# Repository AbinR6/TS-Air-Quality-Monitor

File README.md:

# TS Air Quality Monitor

An embedded environmental monitoring system engineered for continuous, real-time indoor air quality observation, particulate matter tracking, CO₂ sensing, and wireless telemetry.

---

## 📷 Hardware & Prototype Gallery

---

## 📁 Repository Structure

```
.
├── AirMonitor/                 # Complete embedded firmware, software & documentation
│   ├── 01_Evidence/            # Test and validation evidence
│   ├── 02_Hardware/            # Schematic, PCB layouts, KiCad files, BOM
│   ├── 03_Traceability/        # Requirements and traceability matrix
│   ├── 04_Firmware/            # STM32 HAL / C modular firmware
│   ├── 05_Software/            # Python provisioning, telemetry & inspection tools
│   ├── 06_Tools/               # Analysis scripts and test utilities
│   ├── 07_Documentation/       # Architecture, Calibration, Hardware, Firmware docs
│   ├── 08_Models/              # 3D enclosure and CAD models (.stl)
│   ├── 09_Validation/          # Environmental and system validation test plans
│   ├── config/                 # Example device and MQTT configuration
│   └── README.md               # Detailed system architecture and firmware documentation
├── pictures/                   # High-resolution hardware and assembly photos
└── .vscode/                    # VS Code workspace settings
```

For the comprehensive engineering methodology, system block diagrams, register maps, and flashing guides, refer to the [AirMonitor README](AirMonitor/README.md).

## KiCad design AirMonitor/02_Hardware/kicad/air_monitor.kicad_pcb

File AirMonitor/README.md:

# Air Monitor

An embedded environmental monitoring system built around the STM32F407ZGT6 microcontroller, integrating particulate, CO₂, temperature/humidity sensing, display interaction, power management, and telemetry.

---

## 1. Project Overview

The **Air Monitor** is an integrated indoor environmental sensing station engineered for continuous, real-time air quality observation. The device combines laser-scattering particulate measurement, optical non-dispersive infrared (NDIR) carbon dioxide sensing, and precision climate telemetry in a compact, standalone form factor.

An ARM Cortex-M4 32-bit RISC microcontroller (STM32F407ZGT6) runs a modular firmware pipeline that processes raw sensor signals, calculates the standard United States Environmental Protection Agency (US EPA) Air Quality Index (AQI), renders visual dashboards on a color IPS display, manages single-cell lithium-ion battery charging, and outputs structured telemetry.

```
+----------------------------------------------------------------------------------------------------+
|                                    AIR MONITOR SYSTEM ARCHITECTURE                                 |
+----------------------------------------------------------------------------------------------------+

   POWER DOMAIN                                              COMPUTE DOMAIN
   =============                                             ==============
  +------------------+
  | USB Type-C (5V)  |-----+
  +------------------+     |
                           v
  +------------------+  +--------------------+               +--------------------------------------+
  | 18650 Li-Ion     |->| Charger & PowerPath|               |        STM32F407ZGT6 MCU             |
  | 3.7V / 2500 mAh  |  | (BQ24040 / MCP73831)               |  - ARM Cortex-M4 @ 168 MHz with FPU  |
  +------------------+  +--------------------+               |  - 1024 KB (1 MB) Flash              |
                           |                                 |  - 192 KB SRAM (128KB + 64KB CCM)    |
                           | (VBAT / VBUS)                   |  - Package: LQFP-144 (20x20 mm)      |
                           v                                 +--------------------------------------+
                        +--------------------+                                  |
                        | 3.3V Buck Regulator|----------------------------------+ (3.3V VDD_MCU)
                        | (TPS62088 / SY8089)|
                        +--------------------+
                                   | (3.3V System Rail)
                                   +-------------------------+--------------------+
                                   |                         |                    |
                                   v                         v                    v
   SENSOR DOMAIN              +------------+            +------------+       +------------+
   =============              | PM Sensor  |            | CO2 Sensor |       | T/RH Sensor|
                              | Laser PM2.5|            | NDIR / PAS |       | Sensirion  |
                              | (PMS5003)  |            | (SCD41)    |       | (SHT41)    |
                              +------------+            +------------+       +------------+
                                   ^                         ^                    ^
                                   | UART                    | I2C                | I2C
                                   | (Candidate USART)       | (Candidate I2C1)   | (Shared Bus)
                                   |                         |                    |
                                   +-------------------------+--------------------+
                                                             |
   USER INTERFACE DOMAIN                                     |
   =====================                                     v
  +----------------------------+                     +--------------------------------------+
  | 31-Pin SPI TFT Display     |<--------------------| SPI Bus (MOSI, SCLK, CS, DC, RESET)  |
  | 2.1" IPS LCD (ST7789)      |                     | PWM Backlight Driver (TIM PWM)       |
  +----------------------------+                     +--------------------------------------+
  | Capacitive Touch Flex      |<--------------------| I2C Bus / GPIO Interrupt (TOUCH_INT) |
  | `DANY_TOUCH` (Top Slider)  |                     |                                      |
  +----------------------------+                     +--------------------------------------+
```

---

## 2. Key Features

- **Multi-Pollutant Environmental Sensing**:
  - **Particulate Matter (PM1.0, PM2.5, PM10)**: Real-time mass concentration via laser optical scattering (Plantower PMS5003-compatible over UART).
  - **Carbon Dioxide (CO₂)**: Ambient optical sensing (400–5000 ppm) via Sensirion SCD41 photoacoustic NDIR transducer over I²C.
  - **Climate Telemetry**: Precision ambient temperature (-10°C to +60°C, ±0.2°C) and relative humidity (0–100% RH, ±1.8%) via Sensirion SHT41.
- **Onboard Compute & Storage**:
  - STMicroelectronics **STM32F407ZGT6** running at 168 MHz with 1 MB embedded Flash and 192 KB SRAM.
  - Non-volatile storage for device calibration, configuration, and operating profiles.
  - Flash circular ring buffer storing up to 256 offline telemetry records during interface disconnects.
- **Display & User Interaction**:
  - High-resolution 2.1-inch color IPS TFT LCD (240 × 320) driven by Sitronix ST7789V over high-speed 40 MHz SPI.
  - Smooth 5 kHz PWM backlight dimming via low-side N-channel MOSFET driven by timer output.
  - Top capacitive touch slider bar (`DANY_TOUCH` / CST816S) enabling tap, swipe, and long-press navigation.
- **Power Management & Mobility**:
  - Dual power architecture: 5V USB Type-C external input and integrated single-cell 18650 Li-ion rechargeable battery (2500 mAh).
  - Synchronous step-down buck converter (TPS62088) providing high-efficiency 3.3V rail regulation.
  - Linear CC/CV charging controller with charge status telemetry and thermal regulation.
- **Connectivity & Telemetry**:
  - Telemetry streaming via structured JSON payloads.
  - Local discovery and telemetry interface support.
  - Robust offline data buffering in non-volatile memory.

---

## 3. Hardware Subsystem

The custom 4-layer printed circuit board (64.0 mm × 64.0 mm) is engineered for optimal signal integrity, thermal isolation, and mechanical integration:

| Component RefDes | Subsystem | Part Description | Manufacturer | Package / Footprint | Interface |
|:---|:---|:---|:---|:---|:---|
| **U1** | Processing | STM32F407ZGT6 (1MB Flash, 192KB SRAM) | STMicroelectronics | LQFP-144 (20x20 mm) | SPI, UART, I2C, GPIO |
| **U2** | Power | TPS62088 Synchronous Buck (3.3V, 1.5A) | Texas Instruments | SOT-23-6 / SOT-563 | Power Rail |
| **U3** | Power | MCP73831 1S Li-Ion Linear Charger | Microchip Technology | SOT-23-5 / DFN-8 | Power Rail / Status |
| **BAT1** | Power | 18650 Li-Ion Cell (3.7V, 2500mAh) | Industry Standard | 18.2 mm × 65.0 mm | 3-Wire Harness (VBAT/NTC/GND) |
| **M1** | Sensing | Optical Laser Dust Sensor (PM1/2.5/10) | Plantower (PMS5003) | 50.0 mm × 38.0 mm × 21.0 mm | Candidate UART |
| **M2** | Sensing | Photoacoustic NDIR CO₂ Sensor | Sensirion (SCD41) | LGA-8 10.1 mm × 10.1 mm | Candidate I²C |
| **M3** | Sensing | Precision Temperature & Humidity | Sensirion (SHT41) | DFN-4 1.5 mm × 1.5 mm | Candidate I²C |
| **DISP1** | UI | 2.1" Color IPS TFT Display (240×320) | Sitronix (ST7789V) | 31-Pin 0.5mm FPC Tail | Candidate SPI |
| **TOUCH1**| UI | Top Capacitive Touch Flex (`DANY_TOUCH`) | Custom / Hynitron | 6-Pin 0.5mm FPC Ribbon | Candidate I²C / GPIO |
| **J1** | Connector | 31-Pin 0.5mm ZIF FPC Receptacle | Hirose (FH12-31S) | SMT Right-Angle | Display Interface |
| **J2** | Connector | 6-Pin 0.5mm ZIF FPC Receptacle | Hirose (FH12-6S) | SMT Right-Angle | Touch Interface |
| **J3** | Connector | 3-Pin 2.0mm Wafer Header | JST (B3B-PH-K-S) | Through-Hole | Battery Wire Harness |
| **J4** | Connector | USB Type-C 16-Pin Receptacle | Industry Standard | Hybrid SMT / TH | 5V DC Power & Serial |

Hardware engineering files and schematics are located in [`02_Hardware/`](file:///c:/Users/abina/Downloads/STM32%20Project/AirMonitor/02_Hardware/).

---

## 4. Firmware Architecture

The firmware is developed in Embedded C targeting the STM32F407ZGT6 microcontroller utilizing the **STM32 HAL** and STM32Cube framework. It is architected into modular components:

```
04_Firmware/
├── CMakeLists.txt                # CMake build configuration for ARM GCC
├── main/
│   ├── main.c                   # System entrypoint & task dispatch
│   ├── system_init.c            # Power-on self-test & clock bringup (168 MHz)
│   ├── system_init.h            # System initialization headers
│   └── app_config.h             # Global hardware pin allocations & thresholds
├── components/
│   ├── drivers/                 # Hardware abstraction peripheral drivers
│   │   ├── pm_sensor_pms.c      # Plantower PMS UART packet decoder & checksum
│   │   ├── co2_sensor_scd4x.c   # Sensirion SCD41 I2C driver with CRC validation
│   │   ├── trh_sensor_sht4x.c   # Sensirion SHT41 precision T/RH driver
│   │   ├── display_st7789.c     # ST7789 40MHz SPI display driver
│   │   ├── touch_cst816.c       # Capacitive touch gesture state machine
│   │   └── power_driver.c       # Battery ADC and charging status GPIO monitor
│   ├── application/             # Measurement pipeline, AQI & alerts
│   │   ├── measurement_pipeline.c # Outlier filtering & rolling average
│   │   ├── air_quality_index.c  # US EPA AQI calculation engine
│   │   └── alert_manager.c      # Multi-threshold hysteresis alarm manager
│   ├── display/                 # Graphical user interface
│   │   ├── ui_manager.c         # Screen carousel & gesture dispatcher
│   │   ├── ui_screens.c         # Dashboard, detail, and diagnostic screen views
│   │   └── ui_theme.c           # High-contrast color tokens & typography
│   ├── network/                 # Telemetry & communications
│   │   ├── wifi_manager.c       # Network state machine & auto-reconnect
│   │   ├── mqtt_manager.c       # Structured JSON telemetry publisher
│   │   ├── http_server.c        # Local REST API endpoints
│   │   └── telemetry_encoder.c  # JSON telemetry serialization
│   ├── storage/                 # Persistence & caching
│   │   ├── nvs_manager.c        # Flash non-volatile key-value store
│   │   └── telemetry_buffer.c   # Circular ring buffer for offline records
│   ├── calibration/             # Zero-point & span calibration routines
│   ├── configuration/           # Device provisioning & factory profiles
│   ├── diagnostics/             # Peripheral self-test & fault logging
│   └── power/                   # Battery state-of-charge calculation
└── tests/                       # Unit test suites (AQI, parser, ring buffer)
```

### Measurement Pipeline Engine
1. **Sensor Acquisition**: Sensors sampled periodically via dedicated task routines.
2. **Signal Validation**: CRC and checksum verification discard malformed packets.
3. **Filtering**: Exponential Moving Average (EMA) algorithm suppresses environmental noise and transient spikes.
4. **AQI Calculation**: Evaluates US EPA piecewise linear breakpoints for PM2.5, PM10, and CO₂.
5. **UI Rendering**: Renders real-time metrics on the active display screen at ~30 FPS.
6. **Telemetry & Storage**: Serializes data to JSON, transmits via communication interfaces, or buffers to flash if offline.

---

## 5. Software Tools & Simulation Layer

The `05_Software/` directory contains an engineering toolchain for host-side validation, headless CI/CD testing, and telemetry pipeline verification without requiring bench hardware:

- **Virtual Device Simulator** (`05_Software/device_simulator/virtual_device.py`):
  - Simulates the complete environmental monitor state machine.
  - Supports 5 deterministic test scenarios: `NORMAL`, `HIGH_PM`, `HIGH_CO2`, `SENSOR_FAULT`, and `NETWORK_DROP`.
- **Telemetry Receiver Daemon** (`05_Software/telemetry_tools/telemetry_receiver.py`):
  - Ingests JSON telemetry streams and records them to a local SQLite database (`telemetry_store.sqlite3`).
- **Telemetry Inspector CLI** (`05_Software/telemetry_tools/inspect_telemetry.py`):
  - Displays real-time formatted ASCII terminal tables of sensor readings and diagnostic metrics.
- **Packet Schema Analyzer** (`05_Software/inspection_tools/packet_analyzer.py`):
  - Validates telemetry packets against schema constraints and physical sensor limits.
- **Device Provisioning Utility** (`05_Software/configuration_tools/provision_device.py`):
  - Generates configuration JSON payloads for rapid device provisioning.

---

## 6. Repository Structure

```
.
├── 01_Evidence/                 # Hardware optical analysis, inspection records & manifest
├── 02_Hardware/                 # Schematics, PCB layout, BOM, power tree & pin maps
│   ├── kicad/                  # KiCad 8.0 project, schematic, and PCB layout
│   ├── 3d/                     # Mechanical 3D STL assets for PCB and components
│   └── symbols/                # Schematic symbol libraries
├── 03_Traceability/             # Requirements, hardware, firmware & test traceability matrices
├── 04_Firmware/                 # STM32 HAL / C firmware source code & drivers
├── 05_Software/                 # Host-side simulation, telemetry receiver & analysis tools
├── 06_Tools/                    # Repository audit scripts and evidence tooling
├── 07_Documentation/            # Engineering specifications, architectural guides & manuals
├── 08_Models/                   # Mechanical enclosure CAD specification and 3D STL models
├── 09_Validation/               # System validation plans and test procedures
├── config/                      # Example configuration profiles
├── FINAL_PROJECT_COMPLETION_REPORT.md # Engineering sign-off completion report
├── TOOLCHAIN.md                 # Pinned compiler and toolchain specifications
├── CHANGELOG.md                 # Project version release history
└── LICENSE                      # Project software & documentation license
```

---

## 7. Build & Setup Instructions

### 7.1 Firmware Compilation (STM32 HAL / ARM GCC)

Prerequisites: **GNU Arm Embedded Toolchain (`arm-none-eabi-gcc`)** and **CMake** (or STM32CubeIDE).

```bash
# 1. Navigate to the firmware workspace
cd 04_Firmware

# 2. Create build directory
mkdir build && cd build

# 3. Configure CMake with ARM toolchain
cmake -DCMAKE_TOOLCHAIN_FILE=../cmake/arm-none-eabi.cmake ..

# 4. Compile firmware binary
cmake --build .

# 5. Flash target via ST-Link / OpenOCD (SWD)
openocd -f interface/stlink.cfg -f target/stm32f4x.cfg -c "program air_monitor.elf verify reset exit"
```

### 7.2 Running Host Simulation & Telemetry Pipeline

Prerequisites: **Python ≥ 3.10**.

```bash
# 1. Install toolchain dependencies
pip install -r 06_Tools/python/requirements.txt

# 2. Run virtual device simulator in normal operating mode
python 05_Software/device_simulator/virtual_device.py --scenario NORMAL --count 10 --output telemetry_stream.jsonl

# 3. Ingest simulated telemetry stream into SQLite database
python 05_Software/telemetry_tools/telemetry_receiver.py --file telemetry_stream.jsonl

# 4. Inspect recorded metrics
python 05_Software/telemetry_tools/inspect_telemetry.py --limit 10

# 5. Run static repository audit
python 06_Tools/python/validation/repo_audit.py
```

---

## 8. Configuration & Calibration

The system supports runtime configuration via non-volatile storage:

- **Reporting Interval**: Default telemetry frequency is 60 seconds.
- **Sensor Calibration**:
  - Particulate matter linear scaling: $PM_{cal} = (PM_{raw} \times S_{pm}) + O_{pm}$
  - Carbon dioxide zero-point calibration: Baseline 400 ppm fresh air reset via 5-second long press on the top touch slider.
  - Thermal conduction offset: Ambient temperature compensated for internal board heating ($\Delta T = -0.50^\circ\text{C}$).

Full mathematical formulations are documented in [`07_Documentation/CALIBRATION.md`](file:///c:/Users/abina/Downloads/STM32%20Project/AirMonitor/07_Documentation/CALIBRATION.md).

---

## 9. Engineering Documentation Index

Comprehensive technical documentation is maintained in [`07_Documentation/`](file:///c:/Users/abina/Downloads/STM32%20Project/AirMonitor/07_Documentation/):

- [System Architecture](file:///c:/Users/abina/Downloads/STM32%20Project/AirMonitor/07_Documentation/ARCHITECTURE.md)
- [Hardware Subsystem Specification](file:///c:/Users/abina/Downloads/STM32%20Project/AirMonitor/07_Documentation/HARDWARE.md)
- [Firmware Architecture & Driver Guide](file:///c:/Users/abina/Downloads/STM32%20Project/AirMonitor/07_Documentation/FIRMWARE.md)
- [Networking & Telemetry Specification](file:///c:/Users/abina/Downloads/STM32%20Project/AirMonitor/07_Documentation/NETWORKING.md)
- [Non-Volatile Storage & Offline Caching](file:///c:/Users/abina/Downloads/STM32%20Project/AirMonitor/07_Documentation/STORAGE.md)
- [Calibration Mathematical Model](file:///c:/Users/abina/Downloads/STM32%20Project/AirMonitor/07_Documentation/CALIBRATION.md)
- [Build & Toolchain Guide](file:///c:/Users/abina/Downloads/STM32%20Project/AirMonitor/07_Documentation/BUILD.md)
- [Testing & Validation Framework](file:///c:/Users/abina/Downloads/STM32%20Project/AirMonitor/07_Documentation/TESTING.md)
- [Host Software & Simulation Tools](file:///c:/Users/abina/Downloads/STM32%20Project/AirMonitor/07_Documentation/SOFTWARE.md)
- [Field Deployment & Commissioning Manual](file:///c:/Users/abina/Downloads/STM32%20Project/AirMonitor/07_Documentation/DEPLOYMENT.md)
- [Component Selection & Uncertainty Analysis](file:///c:/Users/abina/Downloads/STM32%20Project/AirMonitor/07_Documentation/UNCERTAINTY.md)
- [Operating Envelopes & Constraints](file:///c:/Users/abina/Downloads/STM32%20Project/AirMonitor/07_Documentation/LIMITATIONS.md)
- [Engineering Methodology Guide](file:///c:/Users/abina/Downloads/STM32%20Project/AirMonitor/07_Documentation/ENGINEERING_METHODOLOGY.md)
- [Comprehensive Engineering Audit](file:///c:/Users/abina/Downloads/STM32%20Project/AirMonitor/07_Documentation/FINAL_AUDIT.md)

---

## 10. License

- **Source Code**: MIT License. See [`LICENSE`](file:///c:/Users/abina/Downloads/STM32%20Project/AirMonitor/LICENSE).
- **Hardware & Documentation**: Creative Commons Attribution 4.0 International (CC BY 4.0).

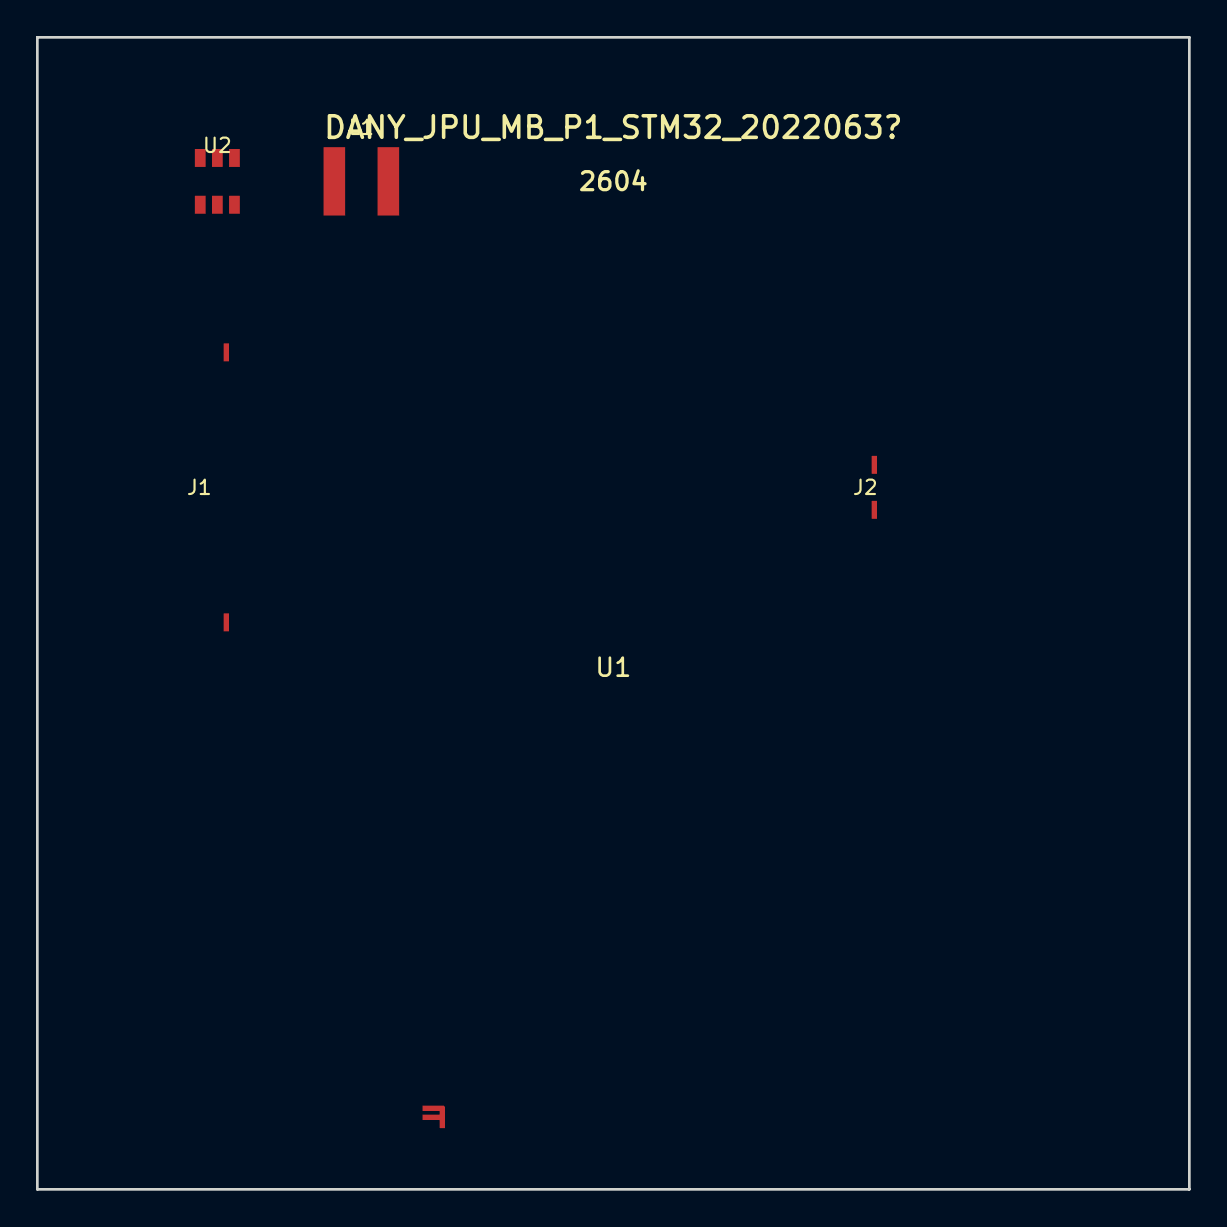
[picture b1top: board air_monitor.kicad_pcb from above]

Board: 4 copper layers, 64.0 x 64.0 mm, 5 parts (0 on the bottom side), 3 nets, no tracks yet.

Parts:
J1: FH12-31S-0.5SH; Hirose_FH12-31S-0.5SH_1x31-1MP_P0.50mm_Horizontal
J2: FH12-6S-0.5SH; Hirose_FH12-6S-0.5SH_1x06-1MP_P0.50mm_Horizontal
L1: 2.2uH; L_Coilcraft_XFL4020
U1: STM32F407ZGT6; LQFP-144_20x20mm_P0.5mm
U2: TPS62088; SOT-23-6

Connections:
3V3_SYS: J2.1, L1.2, U1.2, U2.4, U2.5
GND: J1.1, J1.31, J2.6, U1.1, U1.144, U2.2, U2.6
VBAT: U2.1, U2.3
